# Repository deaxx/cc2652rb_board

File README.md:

# cc2652rb_board
mini dev-board on E72-2G4M05S1F

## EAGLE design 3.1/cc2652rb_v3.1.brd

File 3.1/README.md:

# cc2652rb_board
mini dev-board on E72-2G4M05S1F

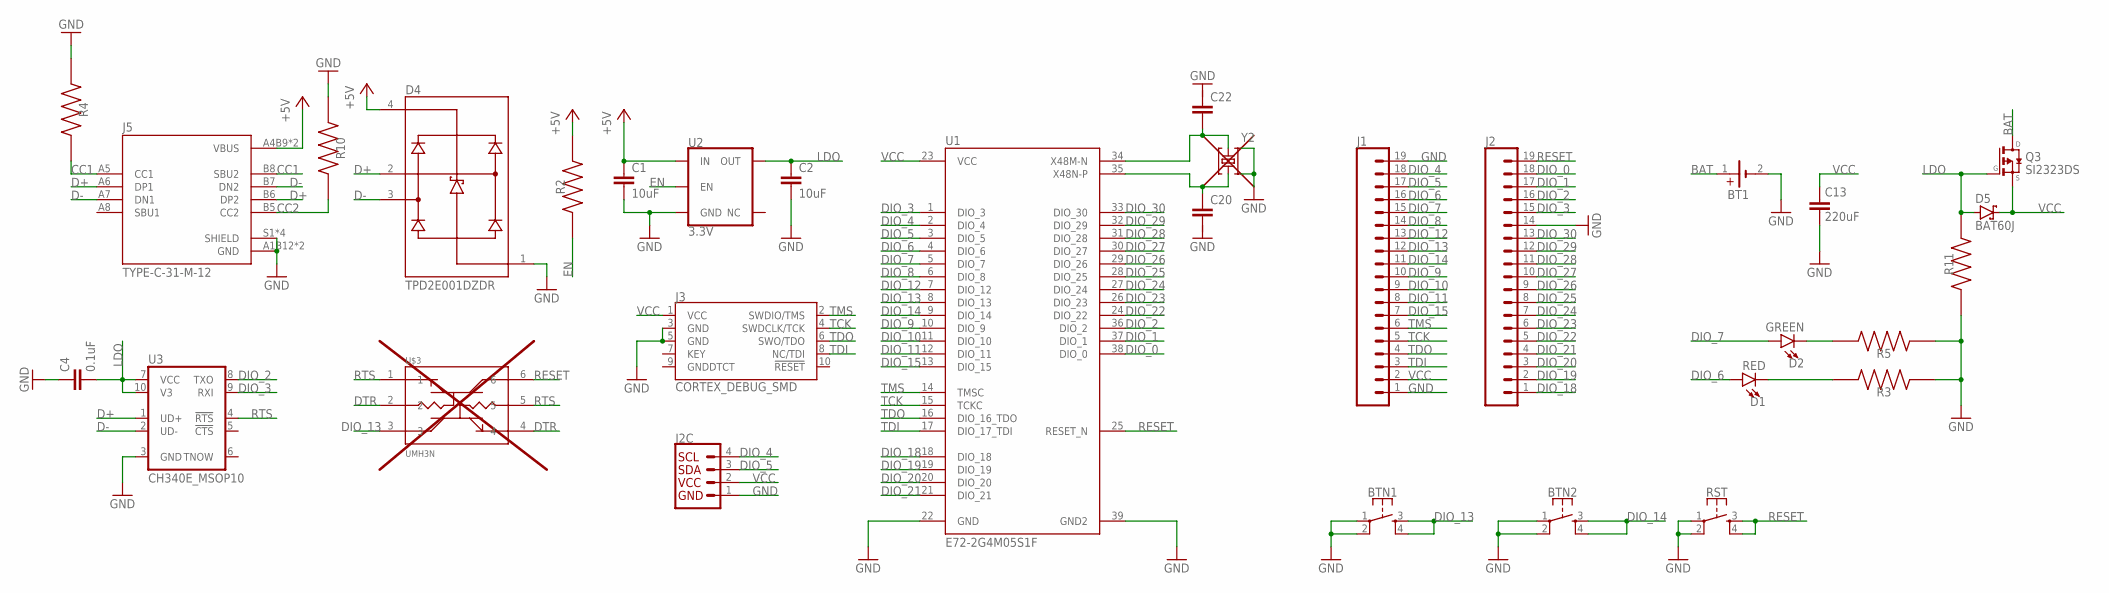
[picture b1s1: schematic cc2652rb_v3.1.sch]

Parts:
BT1: 79527141
BTN1, BTN2: MOMENTARY-SWITCH-SPST-2-SMD-4.6X2.8MM; TACTILE_SWITCH_SMD_4.6X2.8MM
C1, C2: 10uF; 0603
C4: 0.1uF; 0603
C13: 220uF; CAPM7343X310
C20, C22: 7p; CAPC1005X40N
D1: RED; LED-0603
D2: GREEN; LED-0603
D4: TPD2E001DZDR; SOT192P237X122-4N
D5: BAT60J; SOD323_ST
I2C: QWIIC_CONNECTORJS-1MM; 1X04_1MM_RA
J1, J2: CONN_191X19_NO_SILK; 1X19_NO_SILK
J3: CORTEX_DEBUG_SMD; SAMTECH_FTSH-105-01
J5: TYPE-C-31-M-12; HRO_TYPE-C-31-M-12
Q3: SI2323DS; SOT23
R2: 10k; RESC1005X40N
R3, R5: 2k; RESC1005X40N
R4, R10: 5.1k; RESC1005X40N
R11: 100k; RESC1005X40N
RST: MOMENTARY-SWITCH-SPST-2-SMD-4.6X2.8MM; TACTILE_SWITCH_SMD_4.6X2.8MM
U1: E72-2G4M05S1F
U2: 3.3V; SOT23-5
U3: CH340E_MSOP10; MSOP10
U$3: UMH3N; SOP65P210X100-6N
Y2: Q22FA12800150; XTAL-4P-2016

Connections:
+5V: C1.1, D4.4 (VCC), J5.A4B9 (VBUS), J5.B4A9 (VBUS), R2.2, U2.1 (IN)
BAT: BT1.1 (+), Q3.3 (D)
CC1: J5.A5 (CC1), J5.B8 (SBU2), R4.2
CC2: J5.B5 (CC2), R10.2
D+: D4.2 (IO1), J5.A6 (DP1), J5.B6 (DP2), U3.1 (UD+)
D-: D4.3 (IO2), J5.A7 (DN1), J5.B7 (DN2), U3.2 (UD-)
DIO_0: J2.18, U1.38 (DIO_0)
DIO_1: J2.17, U1.37 (DIO_1)
DIO_2: J2.16, U1.36 (DIO_2), U3.8 (TXO)
DIO_3: J2.15, U1.1 (DIO_3), U3.9 (RXI)
DIO_4: I2C.4 (SCL), J1.18, U1.2 (DIO_4)
DIO_5: I2C.3 (SDA), J1.17, U1.3 (DIO_5)
DIO_6: D1.A, J1.16, U1.4 (DIO_6)
DIO_7: D2.A, J1.15, U1.5 (DIO_7)
DIO_8: J1.14, U1.6 (DIO_8)
DIO_9: J1.10, U1.10 (DIO_9)
DIO_10: J1.9, U1.11 (DIO_10)
DIO_11: J1.8, U1.12 (DIO_11)
DIO_12: J1.13, U1.7 (DIO_12)
DIO_13: BTN1.3, BTN1.4, J1.12, U1.8 (DIO_13), U$3.3
DIO_14: BTN2.3, BTN2.4, J1.11, U1.9 (DIO_14)
DIO_15: J1.7, U1.13 (DIO_15)
DIO_18: J2.1, U1.18 (DIO_18)
DIO_19: J2.2, U1.19 (DIO_19)
DIO_20: J2.3, U1.20 (DIO_20)
DIO_21: J2.4, U1.21 (DIO_21)
DIO_22: J2.5, U1.24 (DIO_22)
DIO_23: J2.6, U1.26 (DIO_23)
DIO_24: J2.7, U1.27 (DIO_24)
DIO_25: J2.8, U1.28 (DIO_25)
DIO_26: J2.9, U1.29 (DIO_26)
DIO_27: J2.10, U1.30 (DIO_27)
DIO_28: J2.11, U1.31 (DIO_28)
DIO_29: J2.12, U1.32 (DIO_29)
DIO_30: J2.13, U1.33 (DIO_30)
DTR: U$3.2, U$3.4
EN: R2.1, U2.3 (EN)
GND: BT1.2 (-), BTN1.1, BTN1.2, BTN2.1, BTN2.2, C1.2, C2.2, C4.1, C13.2, D4.1 (GND), I2C.1 (GND), J1.1, J1.19, J2.14, J3.3 (GND), J3.5 (GND), J5.A1B12 (GND), J5.B1A12 (GND), J5.S1 (SHIELD), J5.S2 (SHIELD), J5.S3 (SHIELD), J5.S4 (SHIELD), R3.1, R4.1, R5.1, R10.1, R11.1, RST.1, RST.2, U1.22 (GND), U1.39 (GND2), U2.2 (GND), U3.3 (GND), Y2.2, Y2.4
LDO: C2.1, C4.2, D5.A, Q3.1 (G), R11.2, U2.5 (OUT), U3.7 (VCC), U3.10 (V3)
unnamed: C20.1, U1.35 (X48N-P), Y2.1
unnamed: D1.C, R3.2
unnamed: D2.C, R5.2
unnamed: C22.2, U1.34 (X48M-N), Y2.3
RESET: J2.19, RST.3, RST.4, U1.25 (RESET_N), U$3.6
RTS: U3.4 (!RTS), U$3.1, U$3.5
TCK: J1.5, J3.4 (SWDCLK/TCK), U1.15 (TCKC)
TDI: J1.3, J3.8 (NC/TDI), U1.17 (DIO_17_TDI)
TDO: J1.4, J3.6 (SWO/TDO), U1.16 (DIO_16_TDO)
TMS: J1.6, J3.2 (SWDIO/TMS), U1.14 (TMSC)
VCC: C13.1, D5.C, I2C.2 (VCC), J1.2, J3.1 (VCC), Q3.2 (S), U1.23 (VCC)

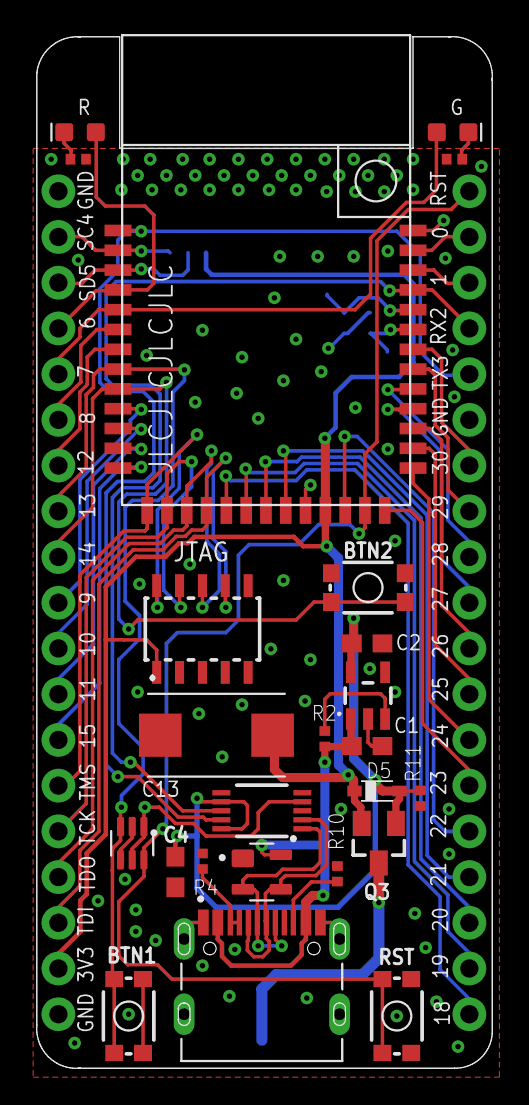
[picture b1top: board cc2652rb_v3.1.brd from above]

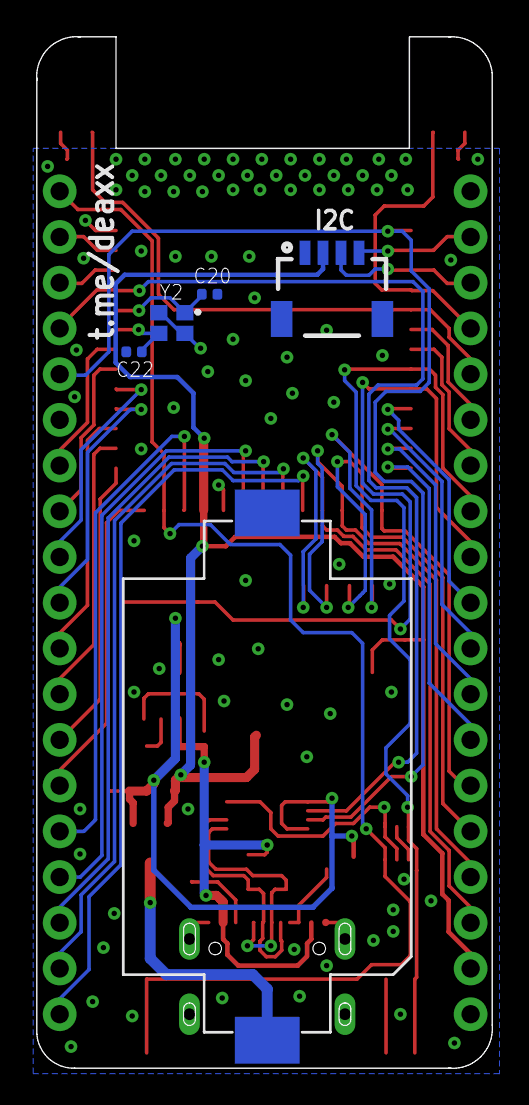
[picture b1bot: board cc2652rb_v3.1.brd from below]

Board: 2 copper layers, 25.3 x 57.3 mm, 31 parts (5 on the bottom side), 50 nets.

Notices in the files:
parts and their libraries:
SparkFun-Connectors: Licensing: Creative Commons ShareAlike 4.0 International - https://creativecommons.org/licenses/by-sa/4.0
